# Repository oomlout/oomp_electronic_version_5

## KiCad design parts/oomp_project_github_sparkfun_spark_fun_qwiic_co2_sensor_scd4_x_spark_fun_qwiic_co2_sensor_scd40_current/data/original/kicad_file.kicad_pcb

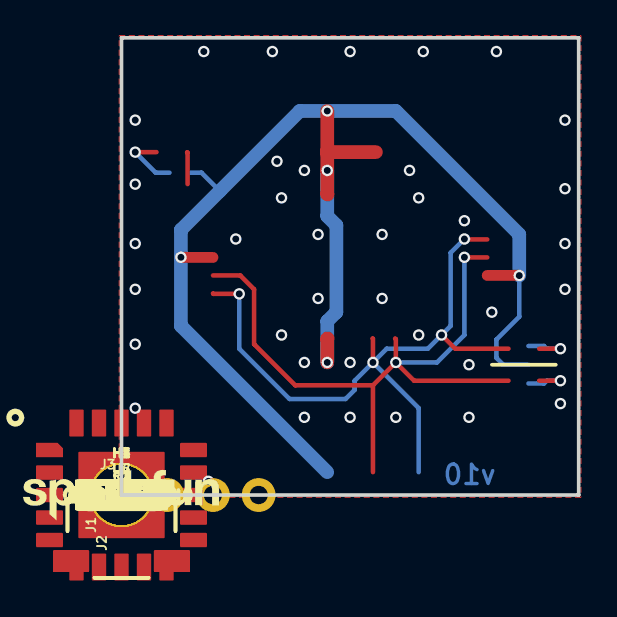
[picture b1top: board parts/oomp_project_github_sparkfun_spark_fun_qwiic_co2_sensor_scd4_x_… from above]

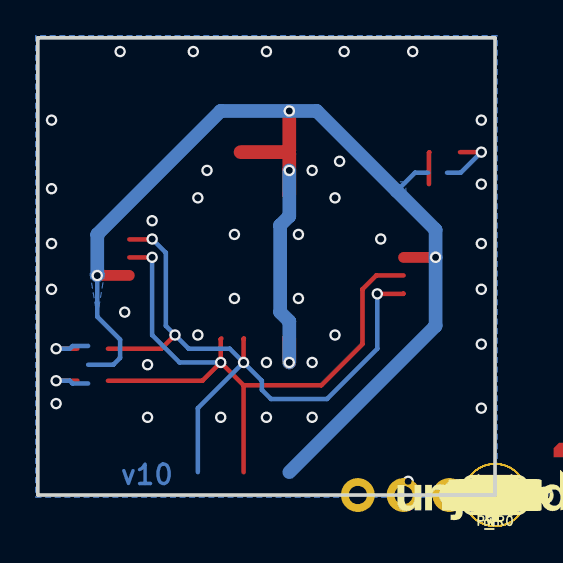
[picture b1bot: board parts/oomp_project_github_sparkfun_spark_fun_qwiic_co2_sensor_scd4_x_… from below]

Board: 2 copper layers, 25.4 x 25.4 mm, 49 parts (16 on the bottom side), 8 nets.

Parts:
C1: 0.1uF; 0603
C2: 4.7uF; 0603
D1: RED; LED-0603
FD1, FD2, FD3, FD4: FIDUCIALUFIDUCIAL; FIDUCIAL-MICRO
FRAME1: FRAME-LETTER; CREATIVE_COMMONS
H1, H2, H3, H4: STAND-OFF
I2C0: I2C; SMT-JUMPER_3_2-NC_TRACE_SILK
J1, J2: QWIIC_RA; JST04_1MM_RA
J3: PTH; 1X04_NO_SILK
LOGO1: QWIIC_LOGO_CONNECTOR; QWIIC_5.5MM
LOGO2: OSHW-LOGOS; OSHW-LOGO-S
LOGO3: SFE_LOGO_NAME_FLAMEBLANK; BLANK
PWR0: PWR; SMT-JUMPER_2_NC_TRACE_SILK
R1, R2: 2.2k; 0603
R3: 4.7k; 0603
U1: SCD40/1; SCD4X
U6: SCD40; PRODUCT_IDENT_PASTE_NO-SILK
U7: SCD41; PRODUCT_IDENT_NO_NO-SILK
U$1, U$18: #_GND#14
U$2, U$19: #_3V3#15
U$3, U$20: #_SDA#15
U$4, U$21: #_SCL#16
U$5, U$12: SFE_LOGO_NAME_.1
U$6: SCD414140404021
U$7: SCD40414140404022
U$8, U$13: QWIIC_CO0
U$9, U$14: SENSOR0
U$10, U$15: 20
U$11: SFE_LOGO_FLAME_STOP_.1
U$16: #PLED#21
U$17: #I�C#0
U$22: ORDERING_INSTRUCTIONS
U$23: PWR0

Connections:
3.3V: C1.1, C2.1, I2C0.2, J1.2, J2.2, J3.2, PWR0.2, U1.7, U1.19
GND: C1.2, C2.2, D1.C, J1.1, J2.1, J3.1, U1.6, U1.20, U1.CP
unnamed: I2C0.1, R2.2
unnamed: I2C0.3, R1.2
unnamed: PWR0.1, R3.2
unnamed: D1.A, R3.1
SCL: J1.4, J2.4, J3.4, R1.1, U1.9
SDA: J1.3, J2.3, J3.3, R2.1, U1.10

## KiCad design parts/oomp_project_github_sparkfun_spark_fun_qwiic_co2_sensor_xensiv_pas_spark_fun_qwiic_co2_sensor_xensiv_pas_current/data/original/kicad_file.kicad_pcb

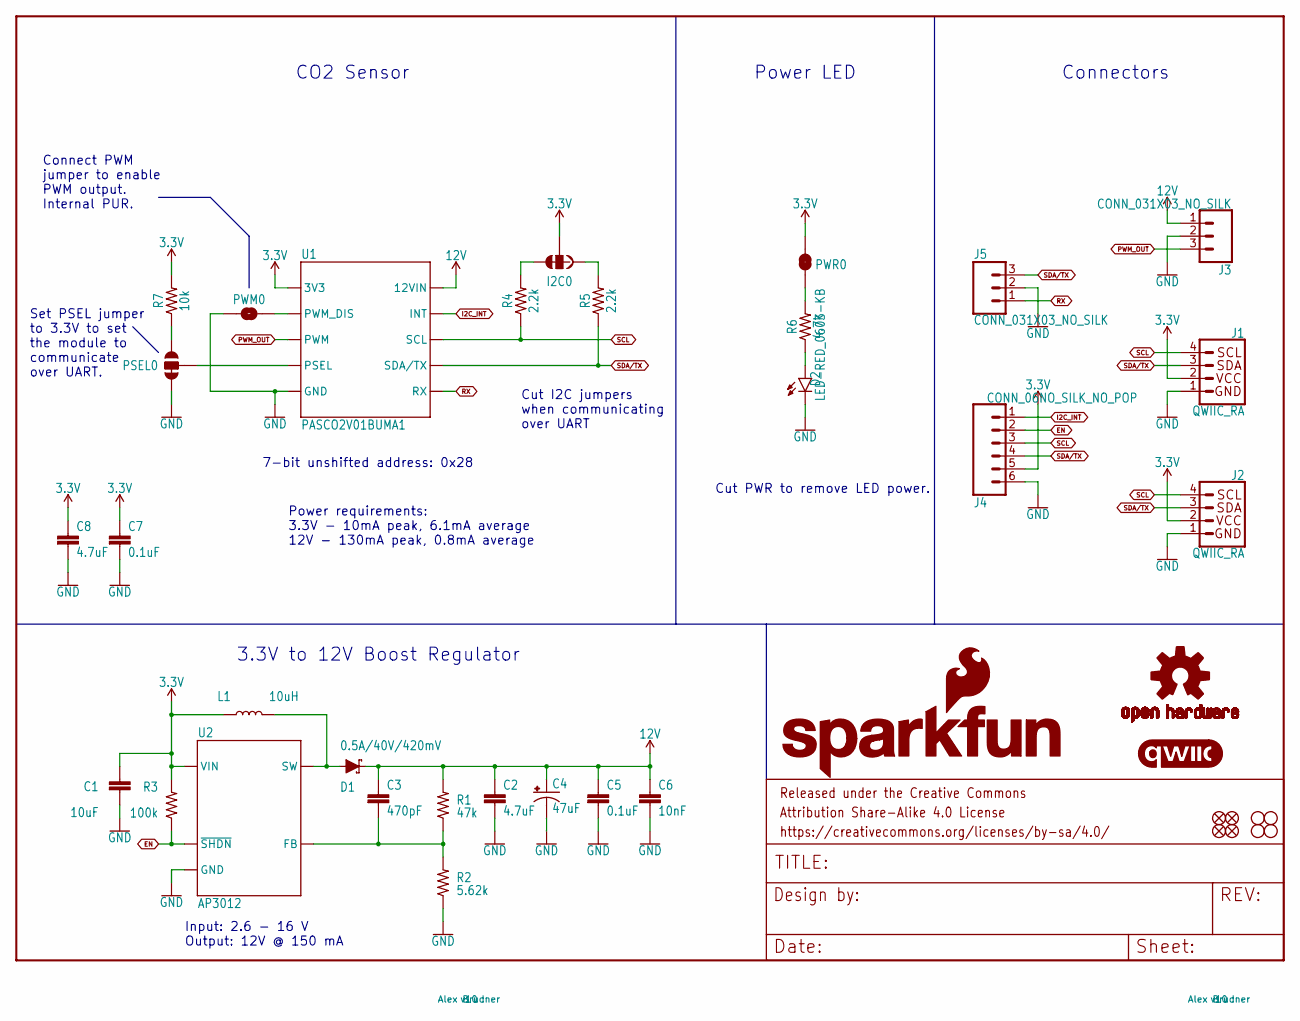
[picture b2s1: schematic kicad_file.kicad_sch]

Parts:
C1: 10uF; 0805
C2, C8: 4.7uF; 0603
C3: 470pF; 0603
C4: 47uF; PANASONIC_D
C5, C7: 0.1uF; 0603
C6: 10nF; 0603
D1: 0.5A/40V/420mV; SOD-323
D2: LED-RED_0603-KB; LED-0603
FD1, FD2, FD3, FD4: FIDUCIALUFIDUCIAL; FIDUCIAL-MICRO
FRAME1: FRAME-LETTER; CREATIVE_COMMONS
H1, H2, H3, H4: STAND-OFF
I2C0: JUMPER-SMT_3_2-NC_TRACE_SILK; SMT-JUMPER_3_2-NC_TRACE_SILK
J1, J2: QWIIC_RA; JST04_1MM_RA
J3, J5: CONN_031X03_NO_SILK; 1X03_NO_SILK
J4: CONN_06NO_SILK_NO_POP; 1X06_NO_SILK
L1: 10uH; 0805
LOGO1: SFE_LOGO_NAME_FLAME.1_INCH; SFE_LOGO_NAME_FLAME_.1
LOGO2: QWIIC_LOGO_5MM; QWIIC_5MM
LOGO3: OSHW-LOGOMINI; OSHW-LOGO-MINI
PSEL0: JUMPER-SMT_3_1-NC_TRACE_SILK; SMT-JUMPER_3_1-NC_TRACE_SILK
PWM0: JUMPER-SMT_2_NO_SILK; SMT-JUMPER_2_NO_SILK
PWR0: JUMPER-SMT_2_NC_TRACE_SILK; SMT-JUMPER_2_NC_TRACE_SILK
R1: 47k; 0603
R2: 5.62k; 0603
R3: 100k; 0603
R4, R5: 2.2k; 0603
R6: 4.7k; 0603
R7: 10k; 0603
U1: PASCO2V01BUMA1; LG-MLGA-14-1_Z8B00206105
U2: AP3012; SOT95P280X145-5M

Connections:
3.3V: C1.1, C7.1, C8.1, I2C0.2, J1.2, J2.2, J4.5, L1.1, PWR0.2, R3.2, R7.2, U1.1 (3V3), U2.5 (VIN)
12V: C2.1, C3.1, C4.+, C5.1, C6.1, D1.C, J3.1, R1.2, U1.10 (12VIN)
EN: J4.2, R3.1, U2.4 (~SHDN)
GND: C1.2, C2.2, C4.-, C5.2, C6.2, C7.2, C8.2, D2.C, J1.1, J2.1, J3.2, J4.6, J5.2, PSEL0.3, PWM0.1, R2.1, U1.6 (GND), U1.11 (GND), U1.12 (GND), U1.13 (GND), U1.14 (GND), U2.2 (GND)
I2C_INT: J4.1, U1.7 (INT)
unnamed: I2C0.1, R5.2
unnamed: D1.A, L1.2, U2.1 (SW)
unnamed: I2C0.3, R4.2
unnamed: C3.2, R1.1, R2.2, U2.3 (FB)
unnamed: PSEL0.2, U1.8 (PSEL)
unnamed: D2.A, R6.1
unnamed: PWR0.1, R6.2
unnamed: PSEL0.1, R7.1
unnamed: PWM0.2, U1.5 (PWM_DIS)
PWM_OUT: J3.3, U1.9 (PWM)
RX: J5.1, U1.2 (RX)
SCL: J1.4, J2.4, J4.3, R4.1, U1.3 (SCL)
SDA/TX: J1.3, J2.3, J4.4, J5.3, R5.1, U1.4 (SDA/TX)

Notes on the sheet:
Cut I2C jumpers when communicating over UART
Power requirements: 3.3V - 10mA peak, 6.1mA average 12V - 130mA peak, 0.8mA average
7-bit unshifted address: 0x28
Connect PWM jumper to enable PWM output. Internal PUR.
Set PSEL jumper to 3.3V to set the module to communicate over UART.
3.3V to 12V Boost Regulator
Cut PWR to remove LED power.
CO2 Sensor
Power LED
Connectors
Input: 2.6 - 16 V Output: 12V @ 150 mA

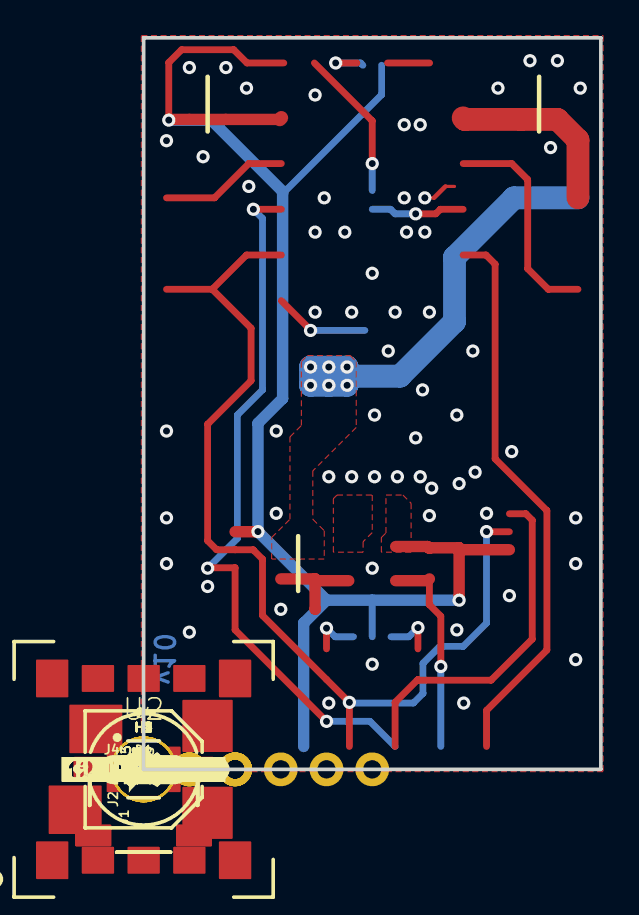
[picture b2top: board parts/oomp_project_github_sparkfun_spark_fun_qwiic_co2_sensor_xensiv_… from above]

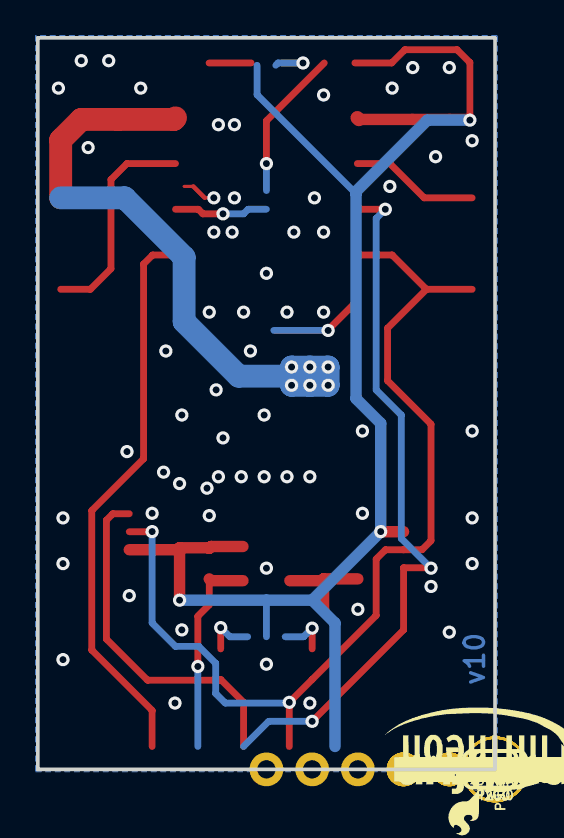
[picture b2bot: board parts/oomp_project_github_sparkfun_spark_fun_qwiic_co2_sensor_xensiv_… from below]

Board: 2 copper layers, 25.4 x 40.6 mm, 80 parts (31 on the bottom side), 18 nets.

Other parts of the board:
U$1: SFE_LOGO_FLAME_.1
U$2: #_12VIN#0
U$3, U$10: #_EN#0
U$4, U$5: #GND_#0
U$6: #_TX#0
U$7: #_RX#0
U$8, U$9, U$14, U$18: #_GND#0
U$11, U$19: #_3V3#0
U$12: #RX_#0
U$13: #SDA#TX_#0
U$15, U$36: #_SCL#0
U$16: #PWM#0
U$17: #P_#0
U$20, U$35: #_SDA#0
U$21, U$22: #_INT#0
U$23: INFINEON_LOGO
U$24: #PSEL#0
U$25: CO2_SENSOR0
U$26: SFE_LOGO_FLAME_STOP_.1
U$27: #I�C#0
U$28: #PWR#0
U$29: PWR0
U$30: ORDERING_INSTRUCTIONS
U$31: #I#0
U$32: #U#0
U$33: #12VI_#0
U$34: #_PWM#0
U$37: PHOTOACOUSTIC0
U$38: SPECTROSCOPY0
U$39: PASCO2V010

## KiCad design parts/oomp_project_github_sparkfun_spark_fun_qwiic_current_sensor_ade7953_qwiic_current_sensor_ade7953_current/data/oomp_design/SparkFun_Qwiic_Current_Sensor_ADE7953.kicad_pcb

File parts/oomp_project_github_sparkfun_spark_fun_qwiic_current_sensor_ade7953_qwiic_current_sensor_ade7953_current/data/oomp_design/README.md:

# OOMP KiCad design copy

Open `SparkFun_Qwiic_Current_Sensor_ADE7953.kicad_pro` (or the `.kicad_pcb` / `.kicad_sch`) in KiCad. Local OOMP libraries are under `libraries/`. Original inputs are preserved in [../original/](../original/).

Only verified unchanged installed KiCad defaults were renamed. Modified, custom, unmatched and unavailable items remain unchanged. Soldering variants are never swapped during conversion. Existing pad coordinates, nets and UUIDs are preserved.

See [conversion_report.yaml](conversion_report.yaml) for every conversion and skip. Copy this directory before editing; regeneration refuses to overwrite edited design files.

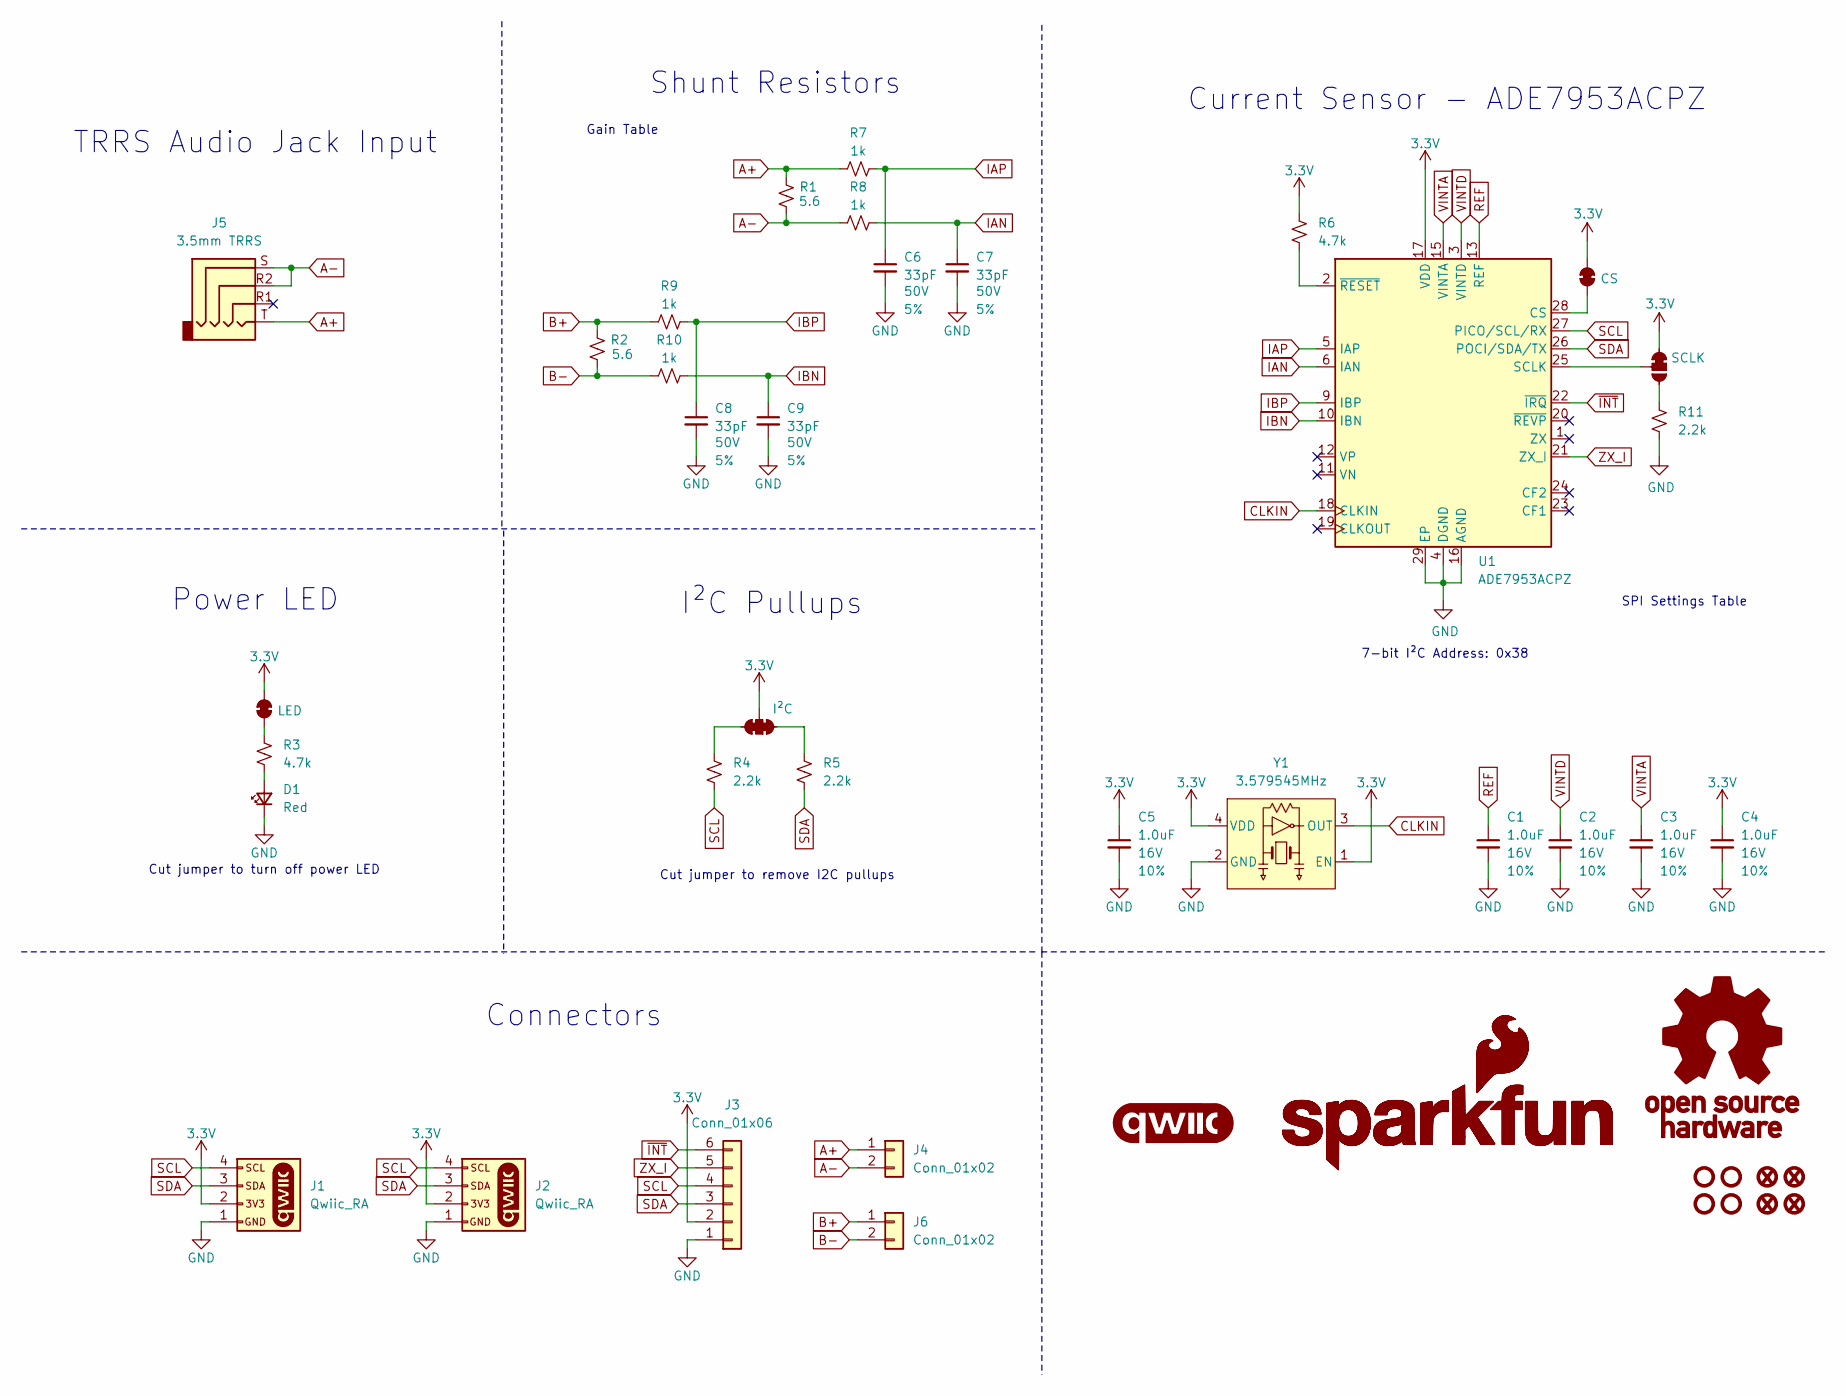
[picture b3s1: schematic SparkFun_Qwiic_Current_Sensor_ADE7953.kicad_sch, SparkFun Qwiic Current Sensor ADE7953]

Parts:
C1, C2, C3, C4, C5: 1.0uF; C_0402_1005Metric; Voltage 16V; Tolerance 10%
C6, C7, C8, C9: 33pF; C_0402_1005Metric; Voltage 50V; Tolerance 5%
D1: Red; LED_0603_1608Metric_Red
FID1, FID2, FID3, FID4: Fiducial_0.5mm; Fiducial_0.5mm_Mask1mm
G1: qwiic_Logo
G2: SparkFun_Logo; SparkFun_Logo_8mm
G3: SparkFun_Logo
G4: OSHW_Logo; Creative_Commons_License
J1, J2: Qwiic_RA; JST_1x04_P1.0mm_Horizontal_SMD
J3: Conn_01x06; 1x06_P2.54mm
J4, J6: Conn_01x02; 1x02_P2.54mm
J5: 3.5mm TRRS; Audio_Jack_3.5mm_TRRS_SMD_RA
JP1: LED; Jumper_2_NC_Trace
JP2: I²C; Jumper_3_NC-2_Trace
JP3: SCLK; Jumper_3_NC-1_Trace
JP4: CS; Jumper_2_NC_Trace
R1, R2: 5.6; R_0603_1608Metric
R3, R6: 4.7k; R_0603_1608Metric
R4, R5, R11: 2.2k; R_0402_1005Metric
R7, R8, R9, R10: 1k; R_0402_1005Metric
ST1, ST2, ST3, ST4: Standoff
U1: ADE7953ACPZ; QFN-28-1EP_4x4_5mmx5mm; Manufacturer_Part_Number ADE7953ACPZ; Mouser Part Number 584-ADE7953ACPZ
Y1: 3.579545MHz; Crystal_SMD_3.2x2.5mm

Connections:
3.3V: C4.1, C5.1, J1.2, J2.2, J3.2, JP1.2 (B), JP2.2 (B), JP3.1 (A), JP4.2 (B), R6.2, U1.7 (PULL_HIGH_1), U1.8 (PULL_HIGH_2), U1.17 (VDD), Y1.1 (EN), Y1.4 (VDD)
A+: J4.1, J5.T, R1.2, R7.1
A-: J4.2, J5.R2, J5.S, R1.1, R8.1
B+: J6.1, R2.2, R9.1
B-: J6.2, R2.1, R10.1
CLKIN: U1.18 (CLKIN), Y1.3 (OUT)
GND: C1.2, C2.2, C3.2, C4.2, C5.2, C6.2, C7.2, C8.2, C9.2, D1.1 (K), J1.1, J2.1, J3.1, R11.1, U1.4 (DGND), U1.14 (PULL_LOW), U1.16 (AGND), U1.29 (EP), Y1.2 (GND)
IAN: C7.1, R8.2, U1.6 (IAN)
IAP: C6.1, R7.2, U1.5 (IAP)
IBN: C9.1, R10.2, U1.10 (IBN)
IBP: C8.1, R9.2, U1.9 (IBP)
unnamed: D1.2 (A), R3.1
unnamed: JP1.1 (A), R3.2
unnamed: JP2.1 (A), R5.2
unnamed: JP2.3 (C), R4.2
unnamed: JP3.2 (B), U1.25 (SCLK)
unnamed: JP3.3 (C), R11.2
unnamed: JP4.1 (A), U1.28 (CS)
unnamed: R6.1, U1.2 (~RESET)
REF: C1.1, U1.13 (REF)
SCL: J1.4, J2.4, J3.4, R4.1, U1.27 (PICO/SCL/RX)
SDA: J1.3, J2.3, J3.3, R5.1, U1.26 (POCI/SDA/TX)
VINTA: C3.1, U1.15 (VINTA)
VINTD: C2.1, U1.3 (VINTD)
ZX_I: J3.5, U1.21 (ZX_I)
~INT: J3.6, U1.22 (~IRQ)

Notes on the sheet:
SPI Settings Table
Current Sensor - ADE7953ACPZ
Shunt Resistors
TRRS Audio Jack Input
7-bit I²C Address: 0x38
Cut jumper to turn off power LED
Power LED
Cut jumper to remove I2C pullups
Gain Table
Connectors
I²C Pullups

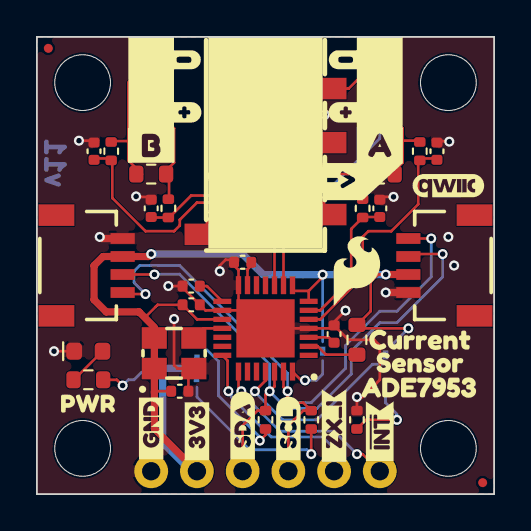
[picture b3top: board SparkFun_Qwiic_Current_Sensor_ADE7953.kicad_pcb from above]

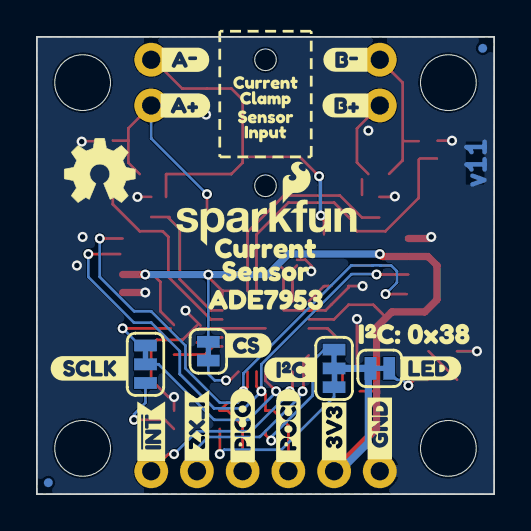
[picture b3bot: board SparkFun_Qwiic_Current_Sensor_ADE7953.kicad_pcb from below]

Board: 2 copper layers, 25.4 x 25.4 mm, 83 parts (29 on the bottom side), 26 nets.

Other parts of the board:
Ref**: Val**; OSHW_Logo_4mm
kibuzzard-6A8F671A: G***; kibuzzard-6A8F671A
kibuzzard-6A8F6918: G***; kibuzzard-6A8F6918
kibuzzard-6A8F6922: G***; kibuzzard-6A8F6922
kibuzzard-6A3051E6: G***; kibuzzard-6A3051E6
kibuzzard-69F8C340: G***; kibuzzard-69F8C340
kibuzzard-69F8FC1F, kibuzzard-69F8FC1F#2: G***; kibuzzard-69F8FC1F
kibuzzard-69F8FC56, kibuzzard-69F8FC56#2: G***; kibuzzard-69F8FC56
kibuzzard-69F8FCF4: G***; kibuzzard-69F8FCF4
kibuzzard-69F8FD80: G***; kibuzzard-69F8FD80
kibuzzard-69FA12A1, kibuzzard-69FA12A1#2: G***; kibuzzard-69FA12A1
kibuzzard-69FA12DB: G***; kibuzzard-69FA12DB
kibuzzard-69FA13A0: G***; kibuzzard-69FA13A0
kibuzzard-69FA13AB: G***; kibuzzard-69FA13AB
kibuzzard-69FA13C4: G***; kibuzzard-69FA13C4
kibuzzard-69FA13D5: G***; kibuzzard-69FA13D5
kibuzzard-69FA128B, kibuzzard-69FA128B#2: G***; kibuzzard-69FA128B
kibuzzard-69FA1293, kibuzzard-69FA1293#2: G***; kibuzzard-69FA1293
kibuzzard-69FCD097: G***; kibuzzard-69FCD097
kibuzzard-69FCDE2E: G***; kibuzzard-69FCDE2E
kibuzzard-69FD0DBC: G***; kibuzzard-69FD0DBC
kibuzzard-69FD0DD3: G***; kibuzzard-69FD0DD3
kibuzzard-69FD0DDA: G***; kibuzzard-69FD0DDA
kibuzzard-69FD0F08: G***; kibuzzard-69FD0F08
kibuzzard-69FD10A0: G***; kibuzzard-69FD10A0
kibuzzard-69FD10AE: G***; kibuzzard-69FD10AE
kibuzzard-69FD1032: G***; kibuzzard-69FD1032
kibuzzard-69FD1060: G***; kibuzzard-69FD1060
kibuzzard-689A66E2: G***; kibuzzard-689A66E2
kibuzzard-689A66E9: G***; kibuzzard-689A66E9
kibuzzard-689A66EE: G***; kibuzzard-689A66EE
kibuzzard-689A66F4: G***; kibuzzard-689A66F4
kibuzzard-689A642E: G***; kibuzzard-689A642E
kibuzzard-689A6721: G***; kibuzzard-689A6721
kibuzzard-689A6728: G***; kibuzzard-689A6728
kibuzzard-689A6796: G***; kibuzzard-689A6796

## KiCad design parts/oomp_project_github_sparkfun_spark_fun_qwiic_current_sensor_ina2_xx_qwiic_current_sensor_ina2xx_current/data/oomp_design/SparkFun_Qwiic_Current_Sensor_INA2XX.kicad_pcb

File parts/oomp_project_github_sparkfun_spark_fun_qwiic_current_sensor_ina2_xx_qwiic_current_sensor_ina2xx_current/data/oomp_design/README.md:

# OOMP KiCad design copy

Open `SparkFun_Qwiic_Current_Sensor_INA2XX.kicad_pro` (or the `.kicad_pcb` / `.kicad_sch`) in KiCad. Local OOMP libraries are under `libraries/`. Original inputs are preserved in [../original/](../original/).

Only verified unchanged installed KiCad defaults were renamed. Modified, custom, unmatched and unavailable items remain unchanged. Soldering variants are never swapped during conversion. Existing pad coordinates, nets and UUIDs are preserved.

See [conversion_report.yaml](conversion_report.yaml) for every conversion and skip. Copy this directory before editing; regeneration refuses to overwrite edited design files.

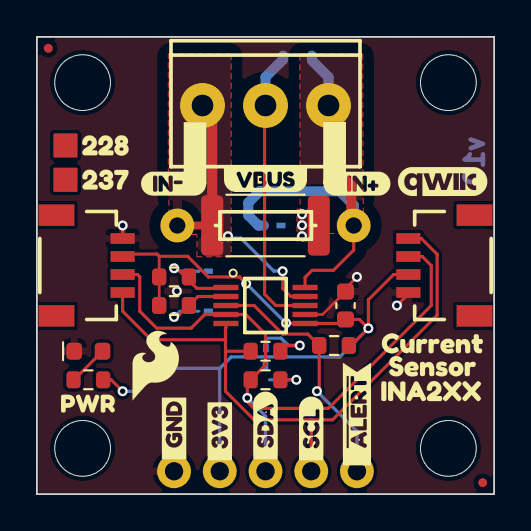
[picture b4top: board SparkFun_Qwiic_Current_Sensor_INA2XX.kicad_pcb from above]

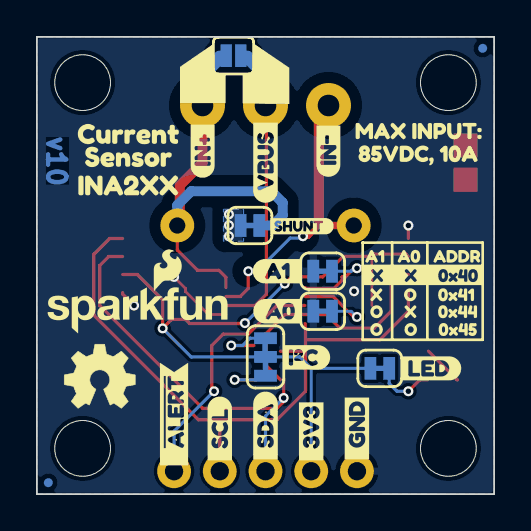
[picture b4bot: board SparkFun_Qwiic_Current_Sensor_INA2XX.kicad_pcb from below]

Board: 2 copper layers, 25.4 x 25.4 mm, 70 parts (32 on the bottom side), 15 nets.

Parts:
C4: 0.1uF; C_0603_1608Metric
D1: Red; LED_0603_1608Metric_Red
FID1, FID2, FID3, FID4: Fiducial_0.5mm; Fiducial_0.5mm_Mask1mm
G4: OSHW_Logo; Creative_Commons_License
J1, J2: Qwiic_RA; JST_1x04_P1.0mm_Horizontal_SMD
J3: Conn_01x06; 1x05_P2.54mm
J5: 3.5mm; ScrewTerminal_1x03_P3.5mm_Horizontal_Black
JP1: LED; Jumper_2_NC_Trace
JP2: I²C; Jumper_3_NC-2_Trace
JP3: SHUNT; Jumper_2_NC_Trace
JP5: A0; Jumper_2_NC_Trace
JP6: A1; Jumper_2_NC_Trace
JP7: VBUS; Jumper_2_NO
R1, R7: 100k; R_0603_1608Metric
R2: 15mR; R_2512_6332Metric
R3: 4.7k; R_0603_1608Metric
R4, R5, R6: 2.2k; R_0603_1608Metric
R8: 10k; R_Axial_DIN0207_L6.3mm_D2.5mm_P7.62mm_Horizontal
Ref**: Val**; TestPoint-1.25mm
Ref**#2: Val**; TestPoint-1.25mm
Ref**#3: Val**; OSHW_Logo_4mm
ST1, ST2, ST3, ST4: Standoff
U2: INA228; SOP-10_4.4x3.6mm_P0.5mm
kibuzzard-6A024EAE: G***; kibuzzard-6A024EAE
kibuzzard-6A024ECD: G***; kibuzzard-6A024ECD
kibuzzard-6A036AB2: G***; kibuzzard-6A036AB2
kibuzzard-6A036AB9: G***; kibuzzard-6A036AB9
kibuzzard-6A036BF8: G***; kibuzzard-6A036BF8
kibuzzard-6A036C03: G***; kibuzzard-6A036C03
kibuzzard-6A036C51: G***; kibuzzard-6A036C51
kibuzzard-6A036C67: G***; kibuzzard-6A036C67
kibuzzard-6A036D6F: G***; kibuzzard-6A036D6F
kibuzzard-6A036D22: G***; kibuzzard-6A036D22
kibuzzard-6A036D59: G***; kibuzzard-6A036D59
kibuzzard-6A036D80: G***; kibuzzard-6A036D80
kibuzzard-6A036E7E: G***; kibuzzard-6A036E7E
kibuzzard-6A038CE2: G***; kibuzzard-6A038CE2
kibuzzard-6A0365C6: G***; kibuzzard-6A0365C6
kibuzzard-6A0369D5: G***; kibuzzard-6A0369D5
kibuzzard-6A0369E2: G***; kibuzzard-6A0369E2
kibuzzard-6A0389D6: G***; kibuzzard-6A0389D6
kibuzzard-6A0389E5: G***; kibuzzard-6A0389E5
kibuzzard-6A036808: G***; kibuzzard-6A036808
kibuzzard-69FA12A1, kibuzzard-69FA12A1#2: G***; kibuzzard-69FA12A1
kibuzzard-69FA1293, kibuzzard-69FA1293#2: G***; kibuzzard-69FA1293
kibuzzard-69FB90BD: G***; kibuzzard-69FB90BD
kibuzzard-69FB860C: G***; kibuzzard-69FB860C
kibuzzard-69FB8600: G***; kibuzzard-69FB8600
kibuzzard-689A66E2: G***; kibuzzard-689A66E2
kibuzzard-689A66E9: G***; kibuzzard-689A66E9
kibuzzard-689A66EE: G***; kibuzzard-689A66EE
kibuzzard-689A66F4: G***; kibuzzard-689A66F4
kibuzzard-689A642E: G***; kibuzzard-689A642E
kibuzzard-689A6711: G***; kibuzzard-689A6711
kibuzzard-689A6718: G***; kibuzzard-689A6718
kibuzzard-689A6721: G***; kibuzzard-689A6721
kibuzzard-689A6728: G***; kibuzzard-689A6728
kibuzzard-689A6796: G***; kibuzzard-689A6796

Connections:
3.3V: C4.1, J1.2, J2.2, J3.2, JP1.2 (B), JP2.2 (B), R1.2, R6.2, R7.2, U2.6 (VS)
A0: JP5.2 (B), R1.1, U2.2 (A0)
A1: JP6.2 (B), R7.1, U2.1 (A1)
GND: C4.2, D1.1 (K), J1.1, J2.1, J3.1, JP5.1 (A), JP6.1 (A), U2.7 (GND)
IN+: J5.1, JP3.2 (B), JP7.2 (B), R8.2, U2.10 (IN+)
IN-: J5.3, R2.2, R8.1, U2.9 (IN-)
unnamed: D1.2 (A), R3.1
unnamed: JP1.1 (A), R3.2
unnamed: JP2.1 (A), R5.2
unnamed: JP2.3 (C), R4.2
unnamed: JP3.1 (A), R2.1
SCL: J1.4, J2.4, J3.4, R4.1, U2.5 (SCL)
SDA: J1.3, J2.3, J3.3, R5.1, U2.4 (SDA)
VBUS: J5.2, JP7.1 (A), U2.8 (VBUS)
~ALERT: J3.5, R6.1, U2.3 (~ALERT)

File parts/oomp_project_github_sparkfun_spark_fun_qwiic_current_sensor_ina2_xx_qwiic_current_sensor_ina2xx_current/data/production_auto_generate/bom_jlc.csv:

Comment,Designator,Footprint,LCSC Part #
0.1uF,C4,SparkFun-Capacitor:C_0603_1608Metric,C14663
100k,"R1,R7",SparkFun-Resistor:R_0603_1608Metric,C25803
10k,R8,SparkFun-Resistor:R_Axial_DIN0207_L6.3mm_D2.5mm_P7.62mm_Horizontal,C2903232
15mR,R2,SparkFun-Resistor:R_2512_6332Metric,
2.2k,"R4,R5,R6",SparkFun-Resistor:R_0603_1608Metric,C4190
3.5mm,J5,SparkFun-Connector:ScrewTerminal_1x03_P3.5mm_Horizontal_Black,
4.7k,R3,SparkFun-Resistor:R_0603_1608Metric,C23162
Conn_01x06,J3,SparkFun-Connector:1x05_P2.54mm,C37208
INA228,U2,SparkFun-Semiconductor-Standard:SOP-10_4.4x3.6mm_P0.5mm,
LED,JP1,SparkFun-Jumper:Jumper_2_NC_Trace,
Qwiic_RA,"J1,J2",SparkFun-Connector:JST_1x04_P1.0mm_Horizontal_SMD,C160404
Red,D1,SparkFun-LED:LED_0603_1608Metric_Red,

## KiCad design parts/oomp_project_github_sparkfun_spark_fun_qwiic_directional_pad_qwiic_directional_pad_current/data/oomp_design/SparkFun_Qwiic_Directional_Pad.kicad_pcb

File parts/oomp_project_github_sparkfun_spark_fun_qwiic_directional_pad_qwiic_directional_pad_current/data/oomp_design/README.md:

# OOMP KiCad design copy

Open `SparkFun_Qwiic_Directional_Pad.kicad_pro` (or the `.kicad_pcb` / `.kicad_sch`) in KiCad. Local OOMP libraries are under `libraries/`. Original inputs are preserved in [../original/](../original/).

Only verified unchanged installed KiCad defaults were renamed. Modified, custom, unmatched and unavailable items remain unchanged. Soldering variants are never swapped during conversion. Existing pad coordinates, nets and UUIDs are preserved.

See [conversion_report.yaml](conversion_report.yaml) for every conversion and skip. Copy this directory before editing; regeneration refuses to overwrite edited design files.

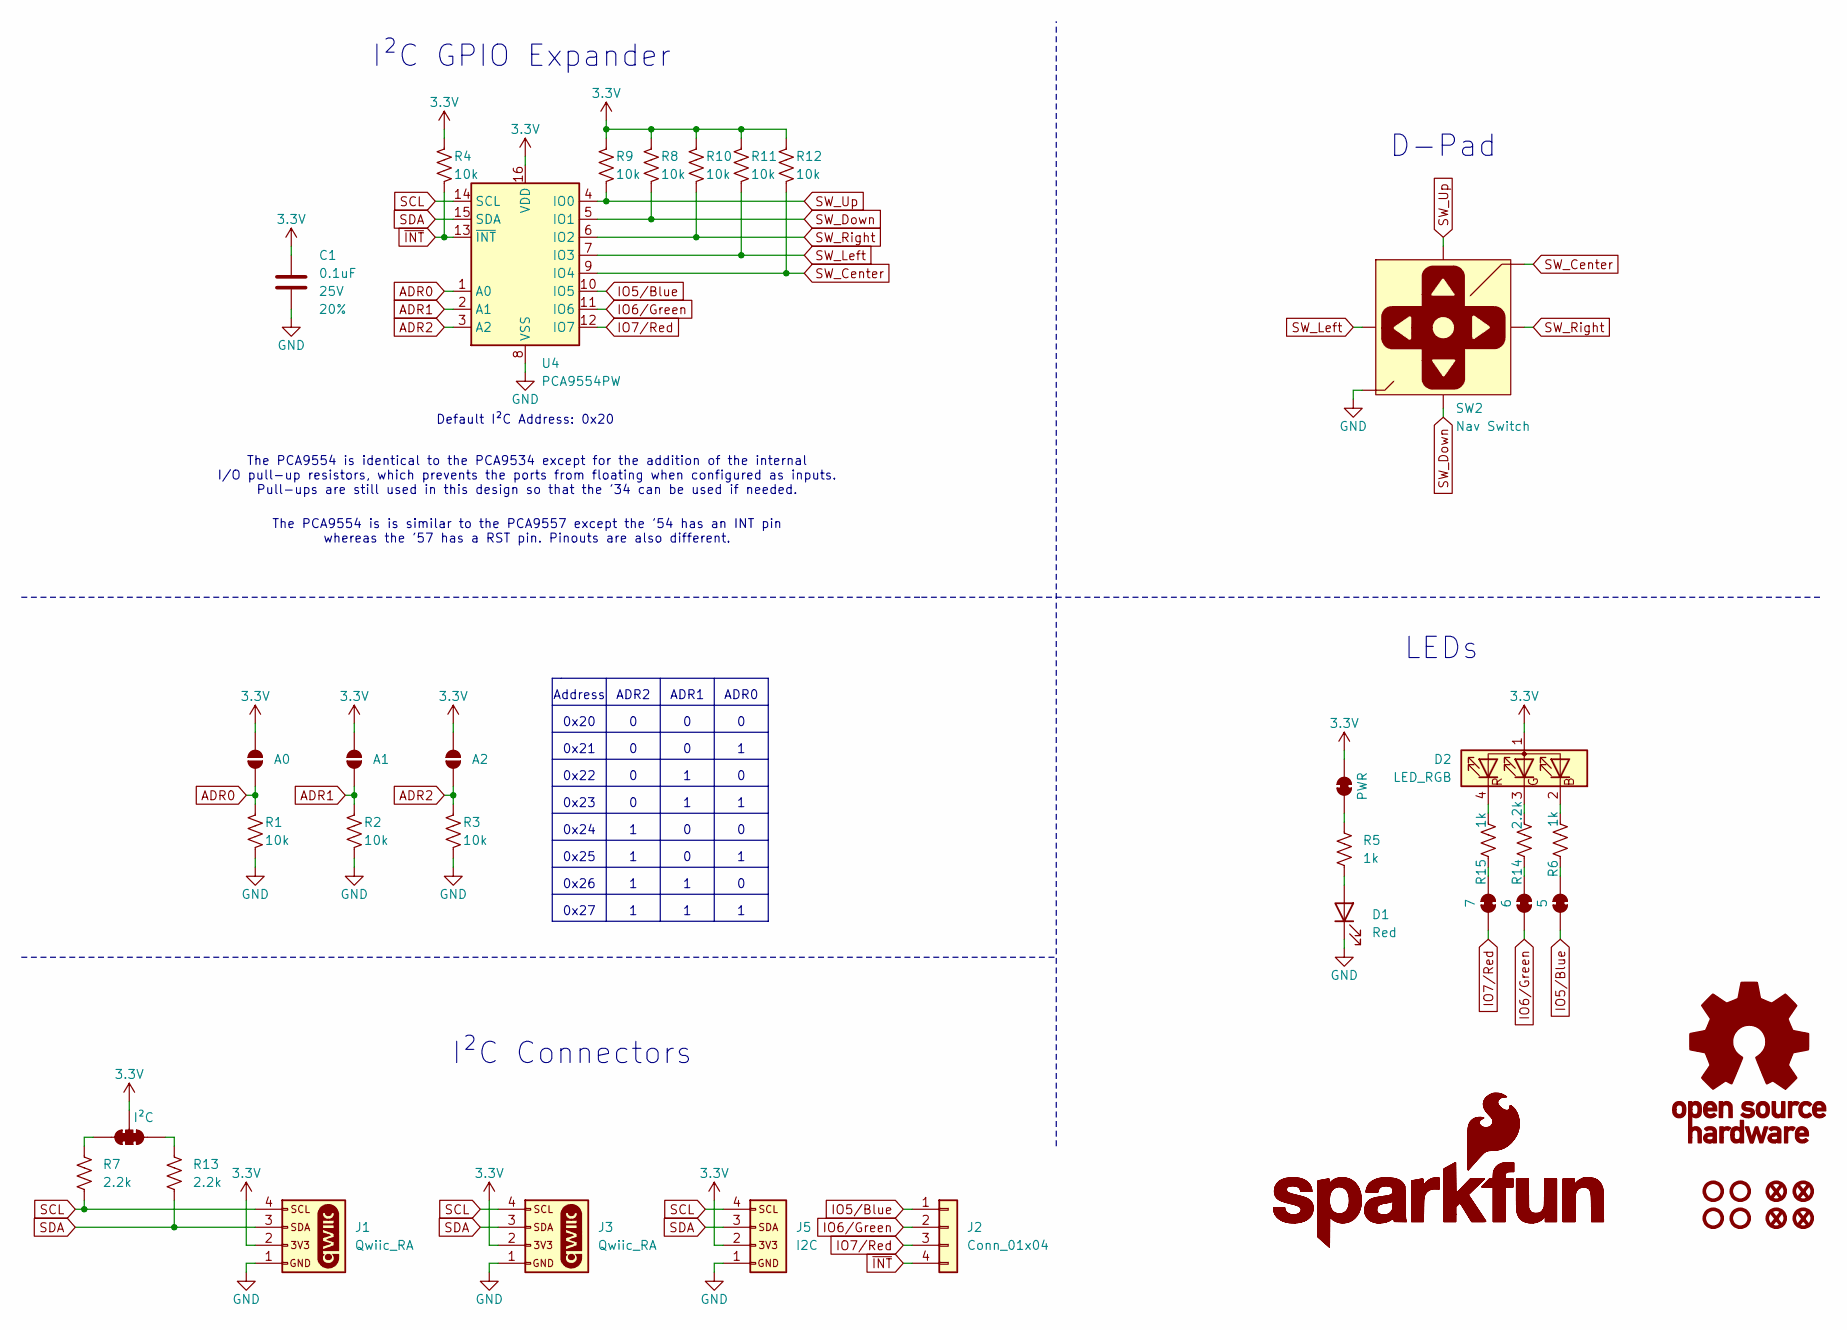
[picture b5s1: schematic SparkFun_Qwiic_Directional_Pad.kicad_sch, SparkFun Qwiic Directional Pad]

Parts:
C1: 0.1uF; C_0603_1608Metric; Voltage 25V; Tolerance 20%
D1: Red; LED_0603_1608Metric_Red
D2: LED_RGB; LED_1205_RGB_Bottom
FID1, FID2, FID3, FID4: Fiducial_0.5mm; Fiducial_0.5mm_Mask1mm
G1: OSHW_Logo; Creative_Commons_License
G3: SparkFun_Logo
G5: SparkFun_Logo; SparkFun_Logo_8mm
J1, J3: Qwiic_RA; JST_SMD_1.0mm-4_RA
J2: Conn_01x04; 1x04
J5: I2C; 1x04
JP1: A0; Jumper_2_NO
JP2: A1; Jumper_2_NO
JP3: A2; Jumper_2_NO
JP4: PWR; Jumper_2_NC_Trace
JP5: 5; Jumper_2_NC_Trace
JP6: I²C; Jumper_3_NC-2_Trace
JP7: 6; Jumper_2_NC_Trace
JP8: 7; Jumper_2_NC_Trace
R1, R2, R3, R4, R8, R9, R10, R11, R12: 10k; R_0603_1608Metric
R5, R6, R15: 1k; R_0603_1608Metric
R7, R13, R14: 2.2k; R_0603_1608Metric
ST1, ST2, ST3, ST4: Standoff
SW2: Nav Switch; Navigation_SMD_9.9x9.9mm
U4: PCA9554PW; TSSOP-16_4.4x5mm_P0.65mm

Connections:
3.3V: C1.1, D2.1 (A), J1.2, J3.2, J5.2, JP1.2 (B), JP2.2 (B), JP3.2 (B), JP4.2 (B), JP6.2 (C), R4.2, R8.2, R9.2, R10.2, R11.2, R12.2, U4.16 (VDD)
ADR0: JP1.1 (A), R1.2, U4.1 (A0)
ADR1: JP2.1 (A), R2.2, U4.2 (A1)
ADR2: JP3.1 (A), R3.2, U4.3 (A2)
GND: C1.2, D1.1 (K), J1.1, J3.1, J5.1, R1.1, R2.1, R3.1, SW2.3 (GND), SW2.6 (GND), SW2.8 (GND), SW2.9 (GND), SW2.10 (GND), U4.8 (VSS)
IO5/Blue: J2.1, JP5.2 (B), U4.10 (IO5)
IO6/Green: J2.2, JP7.2 (B), U4.11 (IO6)
IO7/Red: J2.3, JP8.2 (B), U4.12 (IO7)
unnamed: D1.2 (A), R5.2
unnamed: D2.2 (BK), R6.2
unnamed: D2.3 (GK), R14.2
unnamed: D2.4 (RK), R15.2
unnamed: JP4.1 (A), R5.1
unnamed: JP5.1 (A), R6.1
unnamed: JP6.1 (A), R13.1
unnamed: JP6.3 (B), R7.1
unnamed: JP7.1 (A), R14.1
unnamed: JP8.1 (A), R15.1
SCL: J1.4, J3.4, J5.4, R7.2, U4.14 (SCL)
SDA: J1.3, J3.3, J5.3, R13.2, U4.15 (SDA)
SW_Center: R12.1, SW2.4 (Center), U4.9 (IO4)
SW_Down: R8.1, SW2.5 (Down), U4.5 (IO1)
SW_Left: R11.1, SW2.7 (Left), U4.7 (IO3)
SW_Right: R10.1, SW2.2 (Right), U4.6 (IO2)
SW_Up: R9.1, SW2.1 (Up), U4.4 (IO0)
~INT: J2.4, R4.1, U4.13 (~INT)

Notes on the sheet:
The PCA9554 is is similar to the PCA9557 except the '54 has an INT pin whereas the '57 has a RST pin. Pinouts are also different.
Default I²C Address: 0x20
I²C GPIO Expander
0x20
I²C Connectors
ADR2
ADR0
0x23
The PCA9554 is identical to the PCA9534 except for the addition of the internal I/O pull-up resistors, which prevents the ports from floating when configured as inputs. Pull-ups are still used in this design so that the '34 can be used if needed.
0x22
LEDs
0x25
0x26
0x24
D-Pad
0x27
ADR1
0x21
Address

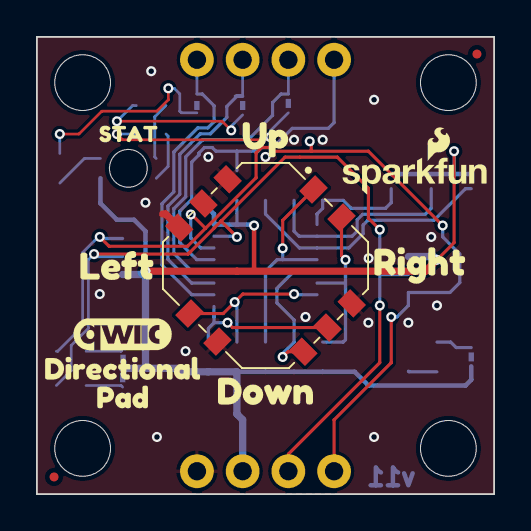
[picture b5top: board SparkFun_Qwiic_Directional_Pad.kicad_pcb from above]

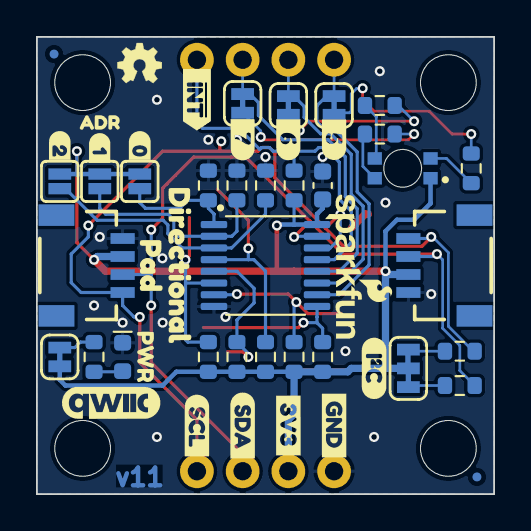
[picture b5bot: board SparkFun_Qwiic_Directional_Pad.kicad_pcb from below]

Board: 2 copper layers, 25.4 x 25.4 mm, 65 parts (48 on the bottom side), 26 nets.

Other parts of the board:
Ref**: Val**; OSHW_Logo_2.5mm
kibuzzard-64C2E6A3: G***; kibuzzard-64C2E6A3
kibuzzard-66EED5D2: G***; kibuzzard-66EED5D2
kibuzzard-66EF6B89: G***; kibuzzard-66EF6B89
kibuzzard-66EF7A0B: G***; kibuzzard-66EF7A0B
kibuzzard-66EF7A03: G***; kibuzzard-66EF7A03
kibuzzard-66EF7A24: G***; kibuzzard-66EF7A24
kibuzzard-66EF7AE6: G***; kibuzzard-66EF7AE6
kibuzzard-66EF7AEF: G***; kibuzzard-66EF7AEF
kibuzzard-66EF7B1E: G***; kibuzzard-66EF7B1E
kibuzzard-66EF7B7C, kibuzzard-66EF7B7C#2: G***; kibuzzard-66EF7B7C
kibuzzard-66EF7B15: G***; kibuzzard-66EF7B15
kibuzzard-66EF7B78, kibuzzard-66EF7B78#2: G***; kibuzzard-66EF7B78
kibuzzard-66EF55AC: G***; kibuzzard-66EF55AC
kibuzzard-66EF79E9: G***; kibuzzard-66EF79E9
kibuzzard-66EF559E: G***; kibuzzard-66EF559E
kibuzzard-66EF5597: G***; kibuzzard-66EF5597
kibuzzard-66F18F5E: G***; kibuzzard-66F18F5E
kibuzzard-66F18F8F: G***; kibuzzard-66F18F8F
kibuzzard-66F18F9B: G***; kibuzzard-66F18F9B
kibuzzard-66F182A6: G***; kibuzzard-66F182A6
kibuzzard-67117BDD: G***; kibuzzard-67117BDD

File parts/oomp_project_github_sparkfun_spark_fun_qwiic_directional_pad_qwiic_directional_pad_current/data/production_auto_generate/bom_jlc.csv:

Comment,Designator,Footprint,LCSC Part #
0.1uF,C1,SparkFun-Capacitor:C_0603_1608Metric,C14663
10k,"R1,R2,R3,R4,R8,R9,R10,R11,R12",SparkFun-Resistor:R_0603_1608Metric,C98220
1k,"R5,R6,R15",SparkFun-Resistor:R_0603_1608Metric,C2907002
2.2k,"R7,R13,R14",SparkFun-Resistor:R_0603_1608Metric,C4190
5,JP5,SparkFun-Jumper:Jumper_2_NC_Trace,
6,JP7,SparkFun-Jumper:Jumper_2_NC_Trace,
7,JP8,SparkFun-Jumper:Jumper_2_NC_Trace,
A0,JP1,SparkFun-Jumper:Jumper_2_NO,
A1,JP2,SparkFun-Jumper:Jumper_2_NO,
A2,JP3,SparkFun-Jumper:Jumper_2_NO,
Conn_01x04,J2,SparkFun-Connector:1x04,C42431795
I2C,J5,SparkFun-Connector:1x04,C42431795
I²C,JP6,SparkFun-Jumper:Jumper_3_NC-2_Trace,
LED_RGB,D2,SparkFun-LED:LED_1205_RGB_Bottom,
Nav Switch,SW2,SparkFun-Switch:Navigation_SMD_9.9x9.9mm,
PCA9554PW,U4,SparkFun-Semiconductor-Standard:TSSOP-16_4.4x5mm_P0.65mm,
PWR,JP4,SparkFun-Jumper:Jumper_2_NC_Trace,
Qwiic_RA,"J1,J3",SparkFun-Connector:JST_SMD_1.0mm-4_RA,C160404
Red,D1,SparkFun-LED:LED_0603_1608Metric_Red,

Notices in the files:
parts/oomp_project_github_sparkfun_spark_fun_qwiic_co2_sensor_scd4_x_spark_fun_qwiic_co2_sensor_scd41_current/data/original/kicad_file.kicad_sch:
Released under the Creative Commons
https://creativecommons.org/licenses/by-sa/4.0
parts and their libraries:
Released under the Creative Commons Attribution Share-Alike 4.0 License
